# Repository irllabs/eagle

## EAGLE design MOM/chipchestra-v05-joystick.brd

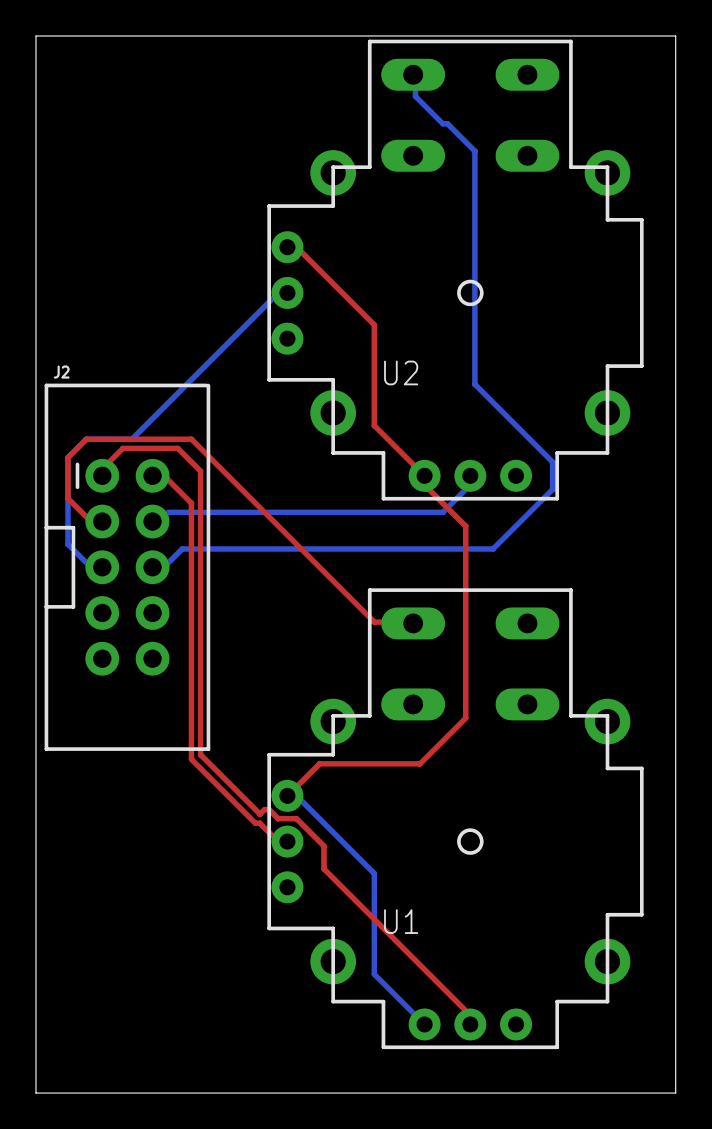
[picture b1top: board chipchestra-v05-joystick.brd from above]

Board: 2 copper layers, 35.5 x 58.7 mm, 3 parts (0 on the bottom side), 8 nets.

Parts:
J2: 2X5-SHROUDED_LOCK
U1, U2: JOYSTICKPTH; JOYSTICK

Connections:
+5V: U1.H1, U1.V1, U2.H1, U2.V1
GND: J2.10, U1.B2A, U1.H3, U1.V3, U2.B2A, U2.H3, U2.V3
JOYB1: J2.3, U1.B1A
JOYB2: J2.6, U2.B1A
JOYH1: J2.1, U1.H2
JOYH2: J2.4, U2.H2
JOYV1: J2.2, U1.V2
JOYV2: J2.5, U2.V2

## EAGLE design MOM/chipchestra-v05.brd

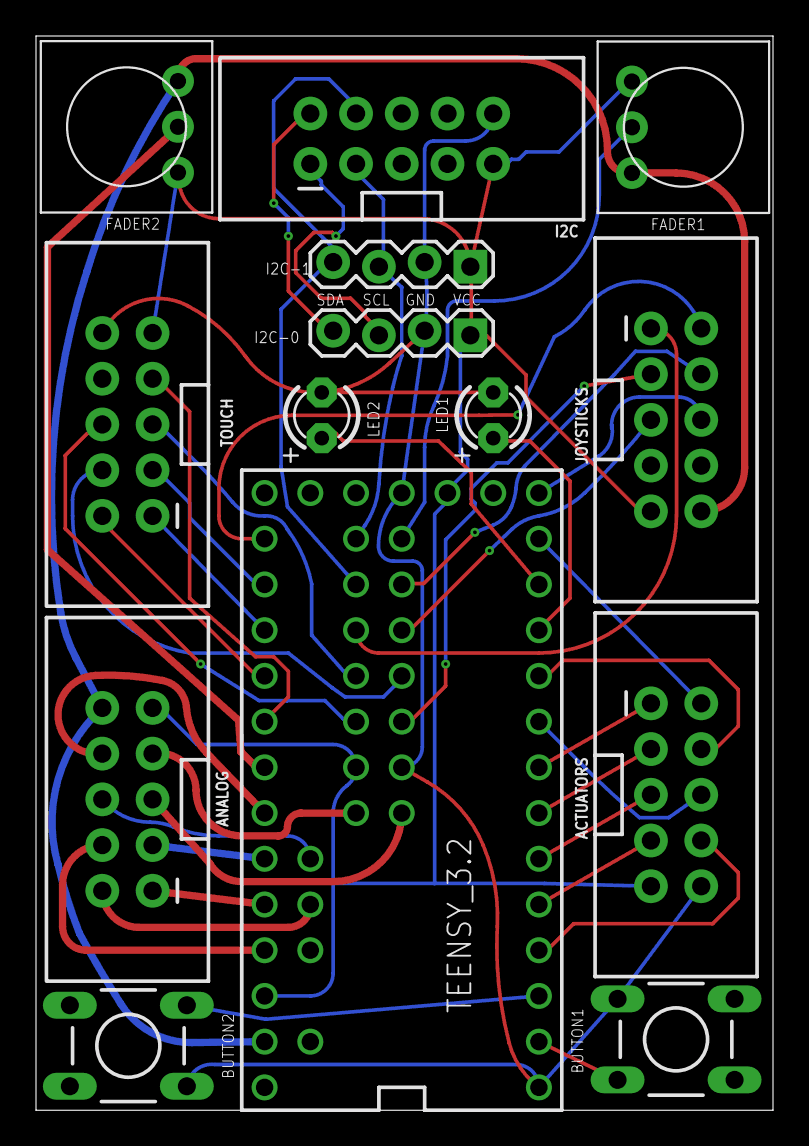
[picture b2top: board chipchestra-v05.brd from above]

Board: 2 copper layers, 40.9 x 59.7 mm, 14 parts (0 on the bottom side), 42 nets.

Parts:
ACTUATORS: 2X5-SHROUDED_LOCK
ANALOG: 2X5-SHROUDED_LOCK
BUTTON1, BUTTON2: DTS-6
FADER1, FADER2: TRIM-3386
I2C: 2X5-SHROUDED_LOCK
I2C-0, I2C-1: 1X04_LOCK
JOYSTICKS: 2X5-SHROUDED_LOCK
LED1, LED2: LED3MM
TEENSY_3.2: TEENSY_3.1-3.2_ALL_PINS&PADS; TEENSY_3.0-3.2_ALL_PINS_&_PADS
TOUCH: 2X5-SHROUDED_LOCK

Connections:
+3V3: ACTUATORS.9, ANALOG.9, FADER1.1, FADER2.1, I2C.9, I2C-0.1, I2C-1.1, JOYSTICKS.9, TEENSY_3.2.3.3V, TEENSY_3.2.3.3V1, TEENSY_3.2.3.3V2, TOUCH.9
AGND: ANALOG.10, FADER1.3, FADER2.3, JOYSTICKS.10, TEENSY_3.2.AGND
ANALOG1: ANALOG.1, TEENSY_3.2.22/A8
ANALOG2: ANALOG.2, TEENSY_3.2.A10
ANALOG3: ANALOG.3, TEENSY_3.2.21/A7
ANALOG4: ANALOG.4, TEENSY_3.2.23/A9
ANALOG5: ANALOG.5, TEENSY_3.2.A12
ANALOG6: ANALOG.6, TEENSY_3.2.A11
ANALOG7: ANALOG.7, TEENSY_3.2.A13
ANALOG8: ANALOG.8, TEENSY_3.2.20/A6
BUTTON1: BUTTON1.3, TEENSY_3.2.0
BUTTON2: BUTTON2.3, TEENSY_3.2.1
FADER1: FADER1.2, TEENSY_3.2.28
FADER2: FADER2.2, TEENSY_3.2.19/A5
GND: ACTUATORS.10, BUTTON1.1, BUTTON2.1, I2C.10, I2C-0.2, I2C-1.2, LED1.K, LED2.K, TEENSY_3.2.GND, TEENSY_3.2.GND1, TEENSY_3.2.GND2, TOUCH.10
I2C_SCL0: I2C.1, I2C-0.3
I2C_SCL1: I2C.3, I2C-1.3, TEENSY_3.2.29
I2C_SDA0: I2C.2, I2C-0.4
I2C_SDA1: I2C.4, I2C-1.4, TEENSY_3.2.30
JOYB1: JOYSTICKS.3, TEENSY_3.2.24
JOYB2: JOYSTICKS.6, TEENSY_3.2.12
JOYH1: JOYSTICKS.1, TEENSY_3.2.31
JOYH2: JOYSTICKS.4, TEENSY_3.2.27
JOYV1: JOYSTICKS.2, TEENSY_3.2.14/A0
JOYV2: JOYSTICKS.5, TEENSY_3.2.26
LED1: LED1.A, TEENSY_3.2.9
LED2: LED2.A, TEENSY_3.2.10
MOT_AIN_1: ACTUATORS.2, TEENSY_3.2.11
MOT_AIN_2: ACTUATORS.6, TEENSY_3.2.7
MOT_BIN_1: ACTUATORS.4, TEENSY_3.2.8
MOT_BIN_2: ACTUATORS.8, TEENSY_3.2.2
MOT_PWMA_1: ACTUATORS.1, TEENSY_3.2.6
MOT_PWMA_2: ACTUATORS.5, TEENSY_3.2.4
MOT_PWMB_1: ACTUATORS.3, TEENSY_3.2.5
MOT_PWMB_2: ACTUATORS.7, TEENSY_3.2.3
TOUCH1: TEENSY_3.2.16/A2, TOUCH.1
TOUCH2: TEENSY_3.2.17/A3, TOUCH.2
TOUCH3: TEENSY_3.2.15/A1, TOUCH.3
TOUCH4: TEENSY_3.2.25, TOUCH.4
TOUCH5: TEENSY_3.2.32, TOUCH.5
TOUCH6: TEENSY_3.2.33, TOUCH.6
TOUCH7: TEENSY_3.2.18/A4, TOUCH.7

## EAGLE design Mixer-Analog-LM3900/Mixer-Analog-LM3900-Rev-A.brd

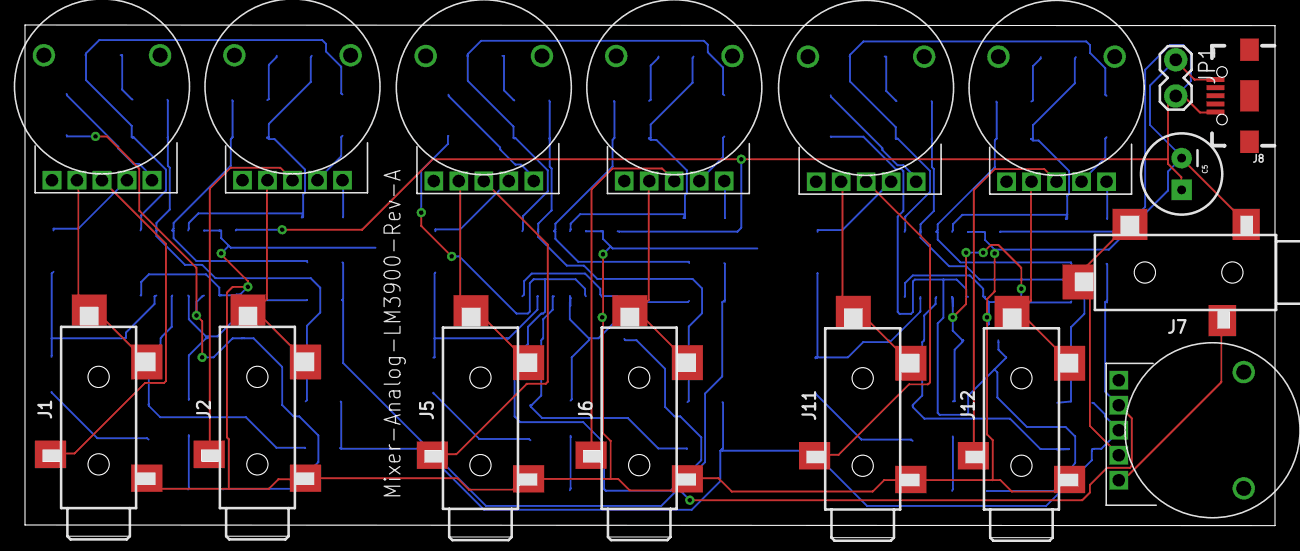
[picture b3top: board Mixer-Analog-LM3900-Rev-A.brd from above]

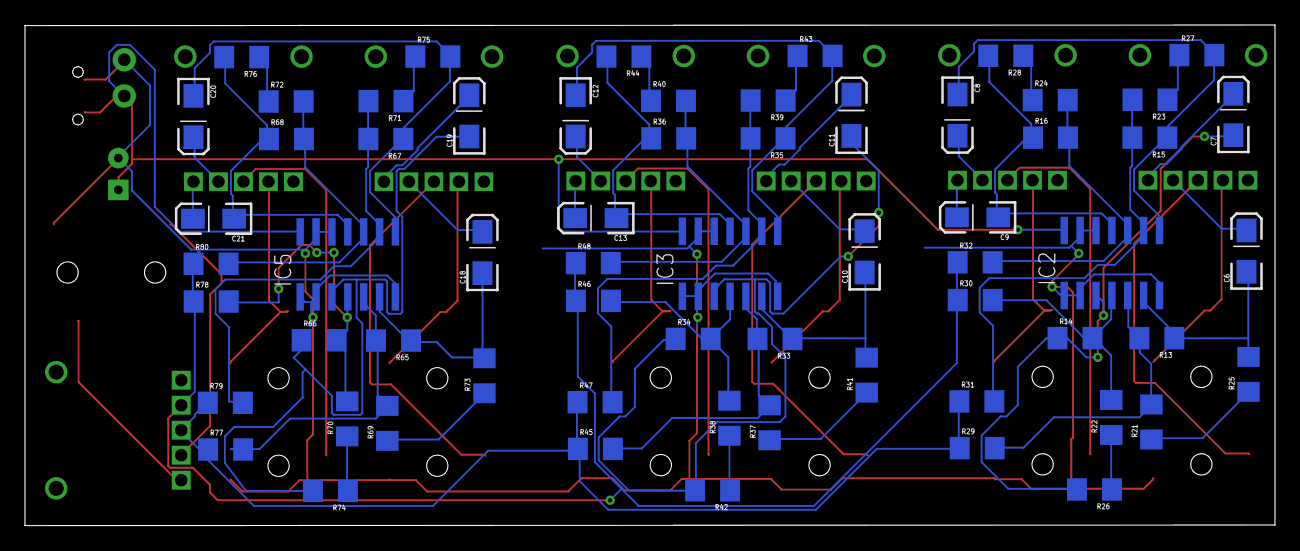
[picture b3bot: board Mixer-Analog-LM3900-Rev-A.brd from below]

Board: 2 copper layers, 100.0 x 40.0 mm, 80 parts (63 on the bottom side), 66 nets.

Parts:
C5: CPOL-RADIAL-100UF-25V
C6, C7, C8, C9, C10, C11, C12, C13, C18, C19, C20, C21: 0.47u; EIA3216-KIT
IC2, IC3, IC5: LM3900D; SO14
J1, J2, J5, J6, J7, J11, J12: SJ-3524-SMT
J8: USB-B-MICRO-SMD
JP1: 1X02_LOCK
R13, R14, R15, R16, R33, R34, R35, R36, R65, R66, R67, R68: 1M; 1206
R21, R22, R23, R24, R37, R38, R39, R40, R69, R70, R71, R72: 330; 1206
R25, R26, R27, R28, R29, R30, R31, R32, R41, R42, R43, R44, R45, R46, R47, R48, R73, R74, R75, R76, R77, R78, R79, R80: 470; 1206
U$3, U$4, U$5, U$6, U$7, U$10, U$11: POT-DUAL-ALPS-RK10J12E0A0A

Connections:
5V: C5.1, IC2.14, IC3.14, IC5.14, J8.VBUS, JP1.2
GND: C5.2, IC2.1, IC2.2, IC2.7, IC2.12, IC2.13, IC3.1, IC3.2, IC3.7, IC3.12, IC3.13, IC5.1, IC5.2, IC5.7, IC5.12, IC5.13, J1.1, J2.1, J5.1, J6.1, J7.1, J8.GND, J11.1, J12.1, JP1.1
unnamed: IC2.5, R13.2, R21.2, R29.2
unnamed: C6.C, IC2.6, R13.1, R25.2
unnamed: R21.1, R25.1
unnamed: IC2.4, R14.2, R22.2, R30.2
unnamed: C7.C, IC2.3, R14.1, R26.2
unnamed: R22.1, R26.1
unnamed: IC2.9, R15.2, R23.2, R31.2
unnamed: C8.C, IC2.8, R15.1, R27.2
unnamed: R23.1, R27.1
unnamed: IC2.10, R16.2, R24.2, R32.2
unnamed: C9.C, IC2.11, R16.1, R28.2
unnamed: R24.1, R28.1
unnamed: C9.A, U$3.P$5
unnamed: C8.A, U$3.P$4
unnamed: C7.A, U$4.P$5
unnamed: C6.A, U$4.P$4
unnamed: J1.2, J1.4, U$4.P$2
unnamed: J2.2, J2.4, U$3.P$2
unnamed: J2.3, U$3.P$3
unnamed: J1.3, U$4.P$3
unnamed: IC3.5, R33.2, R37.2, R45.2
unnamed: C10.C, IC3.6, R33.1, R41.2
unnamed: R37.1, R41.1
unnamed: IC3.4, R34.2, R38.2, R46.2
unnamed: C11.C, IC3.3, R34.1, R42.2
unnamed: R38.1, R42.1
unnamed: IC3.9, R35.2, R39.2, R47.2
unnamed: C12.C, IC3.8, R35.1, R43.2
unnamed: R39.1, R43.1
unnamed: IC3.10, R36.2, R40.2, R48.2
unnamed: C13.C, IC3.11, R36.1, R44.2
unnamed: R40.1, R44.1
unnamed: C13.A, U$5.P$5
unnamed: C12.A, U$5.P$4
unnamed: C11.A, U$6.P$5
unnamed: C10.A, U$6.P$4
unnamed: J5.2, J5.4, U$6.P$2
unnamed: J6.2, J6.4, U$5.P$2
unnamed: J7.2, J7.4, U$7.P$4
unnamed: J7.3, U$7.P$5
unnamed: J6.3, U$5.P$3
unnamed: J5.3, U$6.P$3
unnamed: IC5.5, R65.2, R69.2, R77.2
unnamed: C18.C, IC5.6, R65.1, R73.2
unnamed: R69.1, R73.1
unnamed: IC5.4, R66.2, R70.2, R78.2
unnamed: C19.C, IC5.3, R66.1, R74.2
unnamed: R70.1, R74.1
unnamed: IC5.9, R67.2, R71.2, R79.2
unnamed: C20.C, IC5.8, R67.1, R75.2
unnamed: R71.1, R75.1
unnamed: IC5.10, R68.2, R72.2, R80.2
unnamed: C21.C, IC5.11, R68.1, R76.2
unnamed: R72.1, R76.1
unnamed: C21.A, U$10.P$5
unnamed: C20.A, U$10.P$4
unnamed: C19.A, U$11.P$5
unnamed: C18.A, U$11.P$4
unnamed: J11.2, J11.4, U$11.P$2
unnamed: J12.2, J12.4, U$10.P$2
unnamed: J12.3, U$10.P$3
unnamed: J11.3, U$11.P$3
unnamed: R29.1, R31.1, R45.1, R47.1, R77.1, R79.1, U$7.P$3
unnamed: R30.1, R32.1, R46.1, R48.1, R78.1, R80.1, U$7.P$2

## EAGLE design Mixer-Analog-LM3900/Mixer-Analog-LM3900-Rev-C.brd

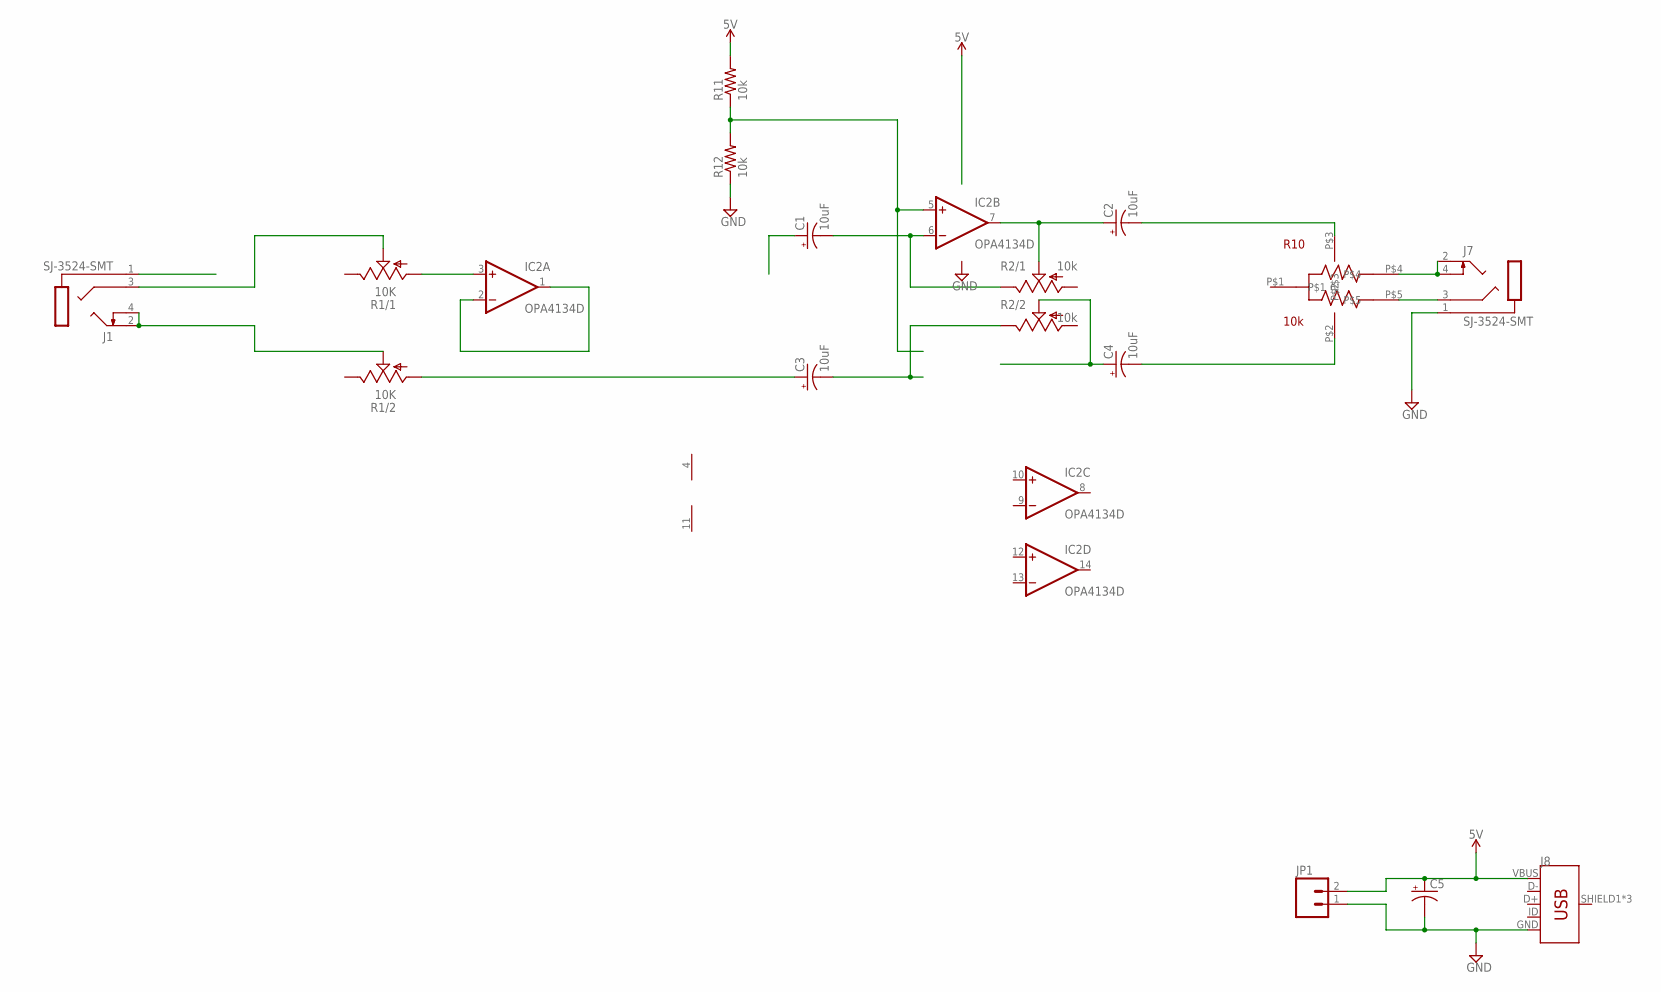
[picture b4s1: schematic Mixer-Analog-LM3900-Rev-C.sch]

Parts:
C1, C2, C3, C4: 10uF; EIA3216-KIT
C5: CAP_POLPTH1; CPOL-RADIAL-100UF-25V
IC2: OPA4134D; SO14
J1, J7: SJ-3524-SMT
J8: USB_MICRO-B_FEMALE-SMT; USB-B-MICRO-SMD
JP1: M02LOCK; 1X02_LOCK
R1: 10K; PTV112
R2: 10k; PTV112
R10: 10k; POT-DUAL-ALPS-RK10J12E0A0A
R11, R12: 10k; 1206

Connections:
5V: C5.1 (+), J8.VBUS, JP1.2, R11.2
DLE: C2.A (+), IC2.7 (OUT), R2.1.2 (S)
GND: C5.2 (-), J7.1 (S), J8.GND, JP1.1, R12.1
unnamed: C3.C (-), R2.2.3 (E)
unnamed: IC2.5 (+IN), R11.1, R12.2
unnamed: IC2.3 (+IN), R1.1.1 (A)
unnamed: IC2.1 (OUT), IC2.2 (-IN)
unnamed: C4.C (-), R10.P$2
unnamed: C1.C (-), IC2.6 (-IN), R2.1.3 (E)
unnamed: C4.A (+), R2.2.2 (S)
unnamed: C3.A (+), R1.2.1 (A)
unnamed: J1.2 (T), J1.4 (TS), R1.2.2 (S)
unnamed: J1.3 (R), R1.1.2 (S)
unnamed: J7.2 (T), J7.4 (TS), R10.P$4
unnamed: J7.3 (R), R10.P$5
unnamed: C2.C (-), R10.P$3
V+: IC2.4 (V+)
V-: IC2.11 (V-)

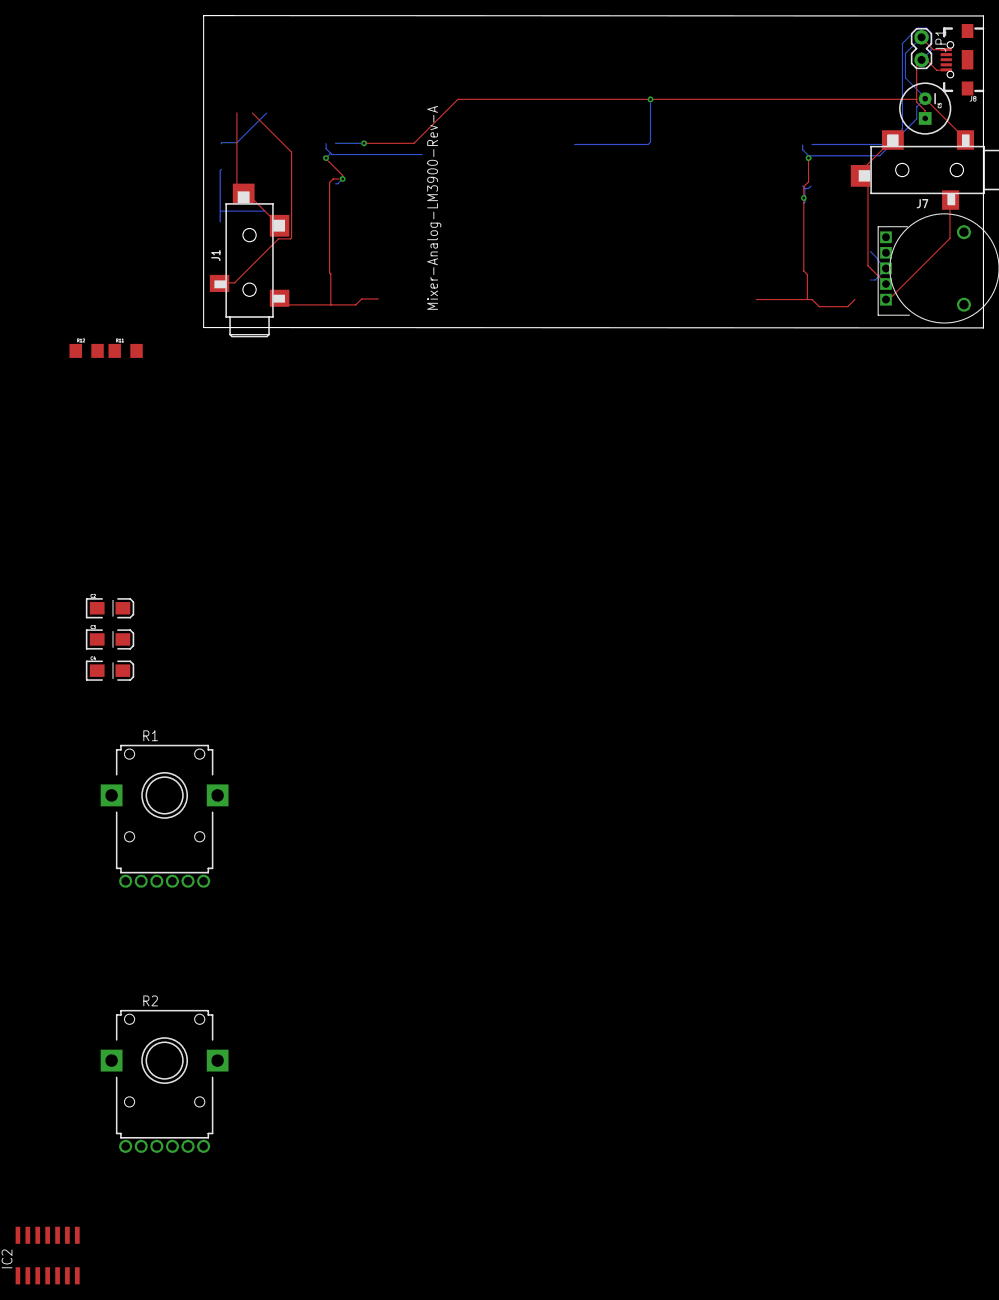
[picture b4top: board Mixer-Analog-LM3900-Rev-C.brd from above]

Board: 2 copper layers, 100.0 x 40.0 mm, 15 parts (1 on the bottom side), 16 nets.

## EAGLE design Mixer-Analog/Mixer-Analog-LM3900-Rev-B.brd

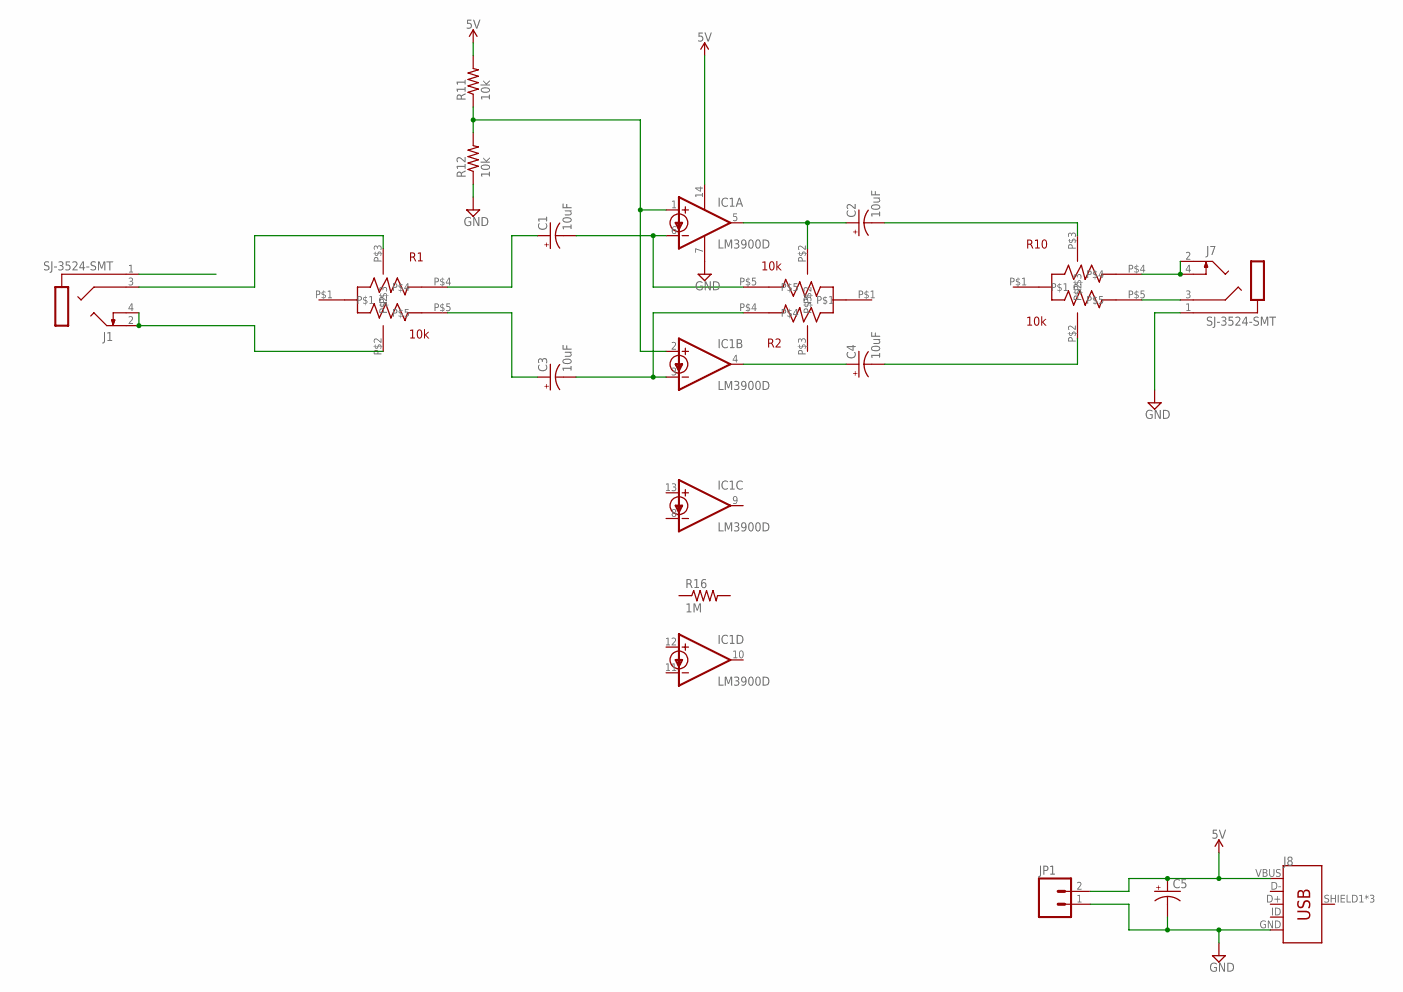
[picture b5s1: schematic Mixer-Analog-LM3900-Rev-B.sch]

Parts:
C1, C2, C3, C4: 10uF; EIA3216-KIT
C5: CAP_POLPTH1; CPOL-RADIAL-100UF-25V
IC1: LM3900D; SO14
J1, J7: SJ-3524-SMT
J8: USB_MICRO-B_FEMALE-SMT; USB-B-MICRO-SMD
JP1: M02LOCK; 1X02_LOCK
R1, R2, R10: 10k; POT-DUAL-ALPS-RK10J12E0A0A
R11, R12: 10k; 1206
R16: 1M; 1206

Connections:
5V: C5.1 (+), IC1.14 (V+), J8.VBUS, JP1.2, R11.2
GND: C5.2 (-), IC1.7 (GND), J7.1 (S), J8.GND, JP1.1, R12.1
unnamed: C3.C (-), IC1.3 (-IN), R2.P$4
unnamed: IC1.1 (+IN), IC1.2 (+IN), R11.1, R12.2
unnamed: C4.C (-), R10.P$2
unnamed: C2.A (+), IC1.5 (OUT), R2.P$2
unnamed: C1.C (-), IC1.6 (-IN), R2.P$5
unnamed: C4.A (+), IC1.4 (OUT)
unnamed: C3.A (+), R1.P$5
unnamed: C1.A (+), R1.P$4
unnamed: J1.2 (T), J1.4 (TS), R1.P$2
unnamed: J1.3 (R), R1.P$3
unnamed: J7.2 (T), J7.4 (TS), R10.P$4
unnamed: J7.3 (R), R10.P$5
unnamed: C2.C (-), R10.P$3

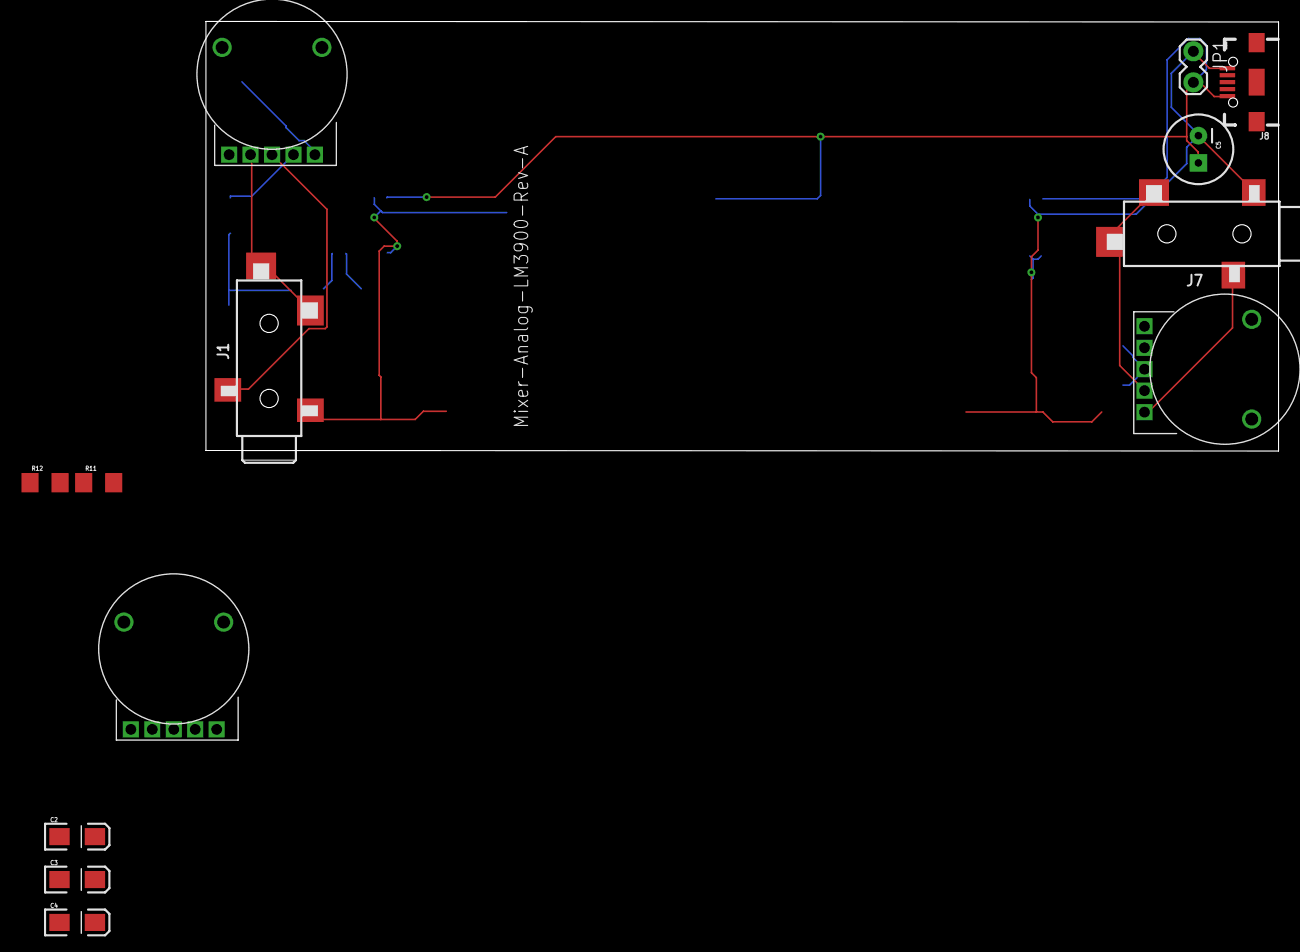
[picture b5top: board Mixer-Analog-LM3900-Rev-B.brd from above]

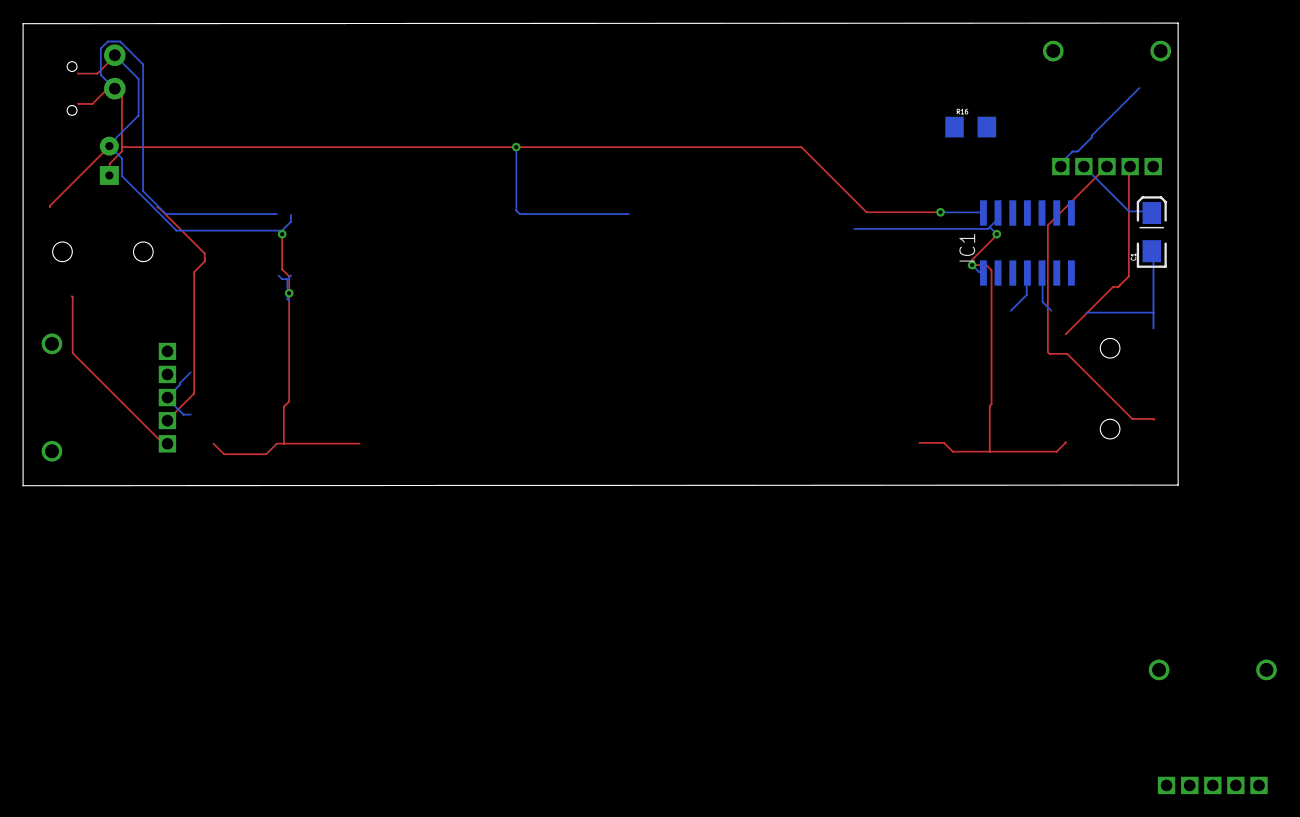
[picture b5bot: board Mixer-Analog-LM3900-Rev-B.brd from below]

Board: 2 copper layers, 100.0 x 40.0 mm, 16 parts (3 on the bottom side), 15 nets.

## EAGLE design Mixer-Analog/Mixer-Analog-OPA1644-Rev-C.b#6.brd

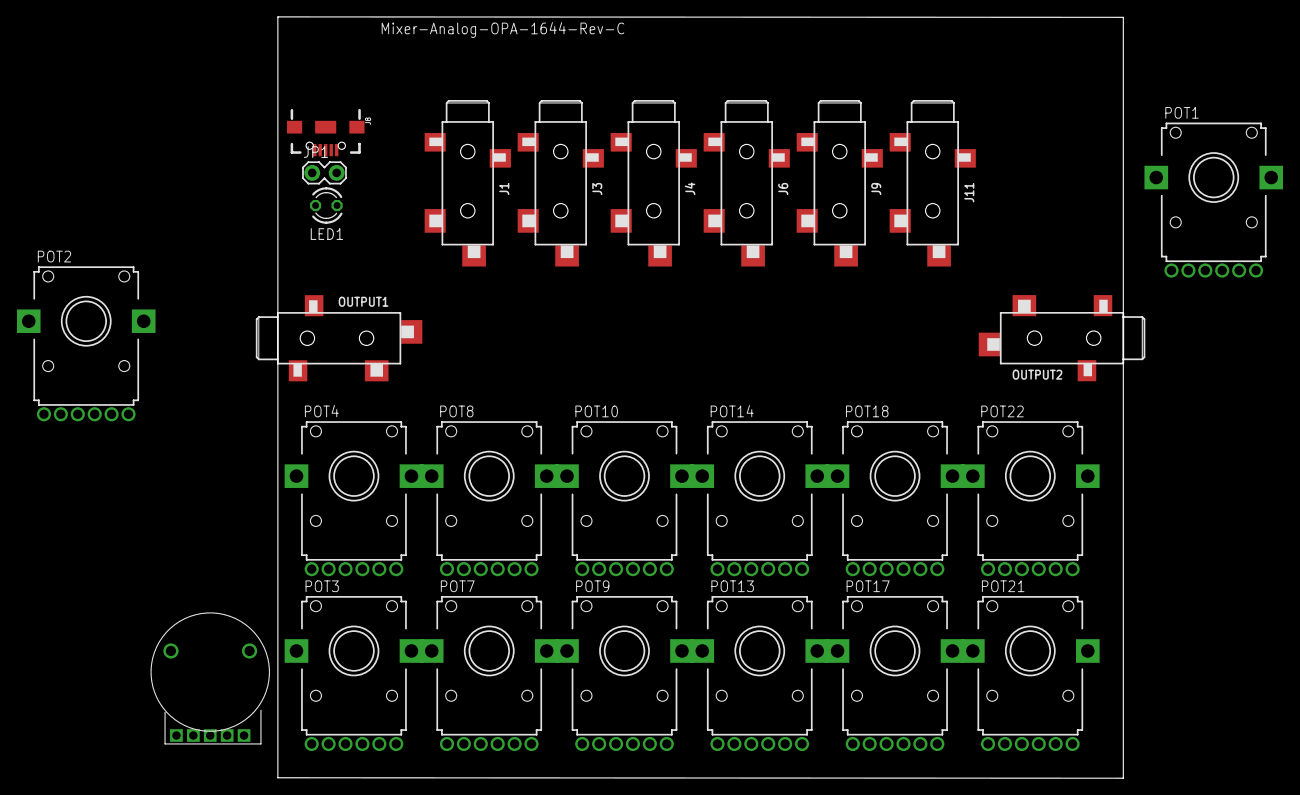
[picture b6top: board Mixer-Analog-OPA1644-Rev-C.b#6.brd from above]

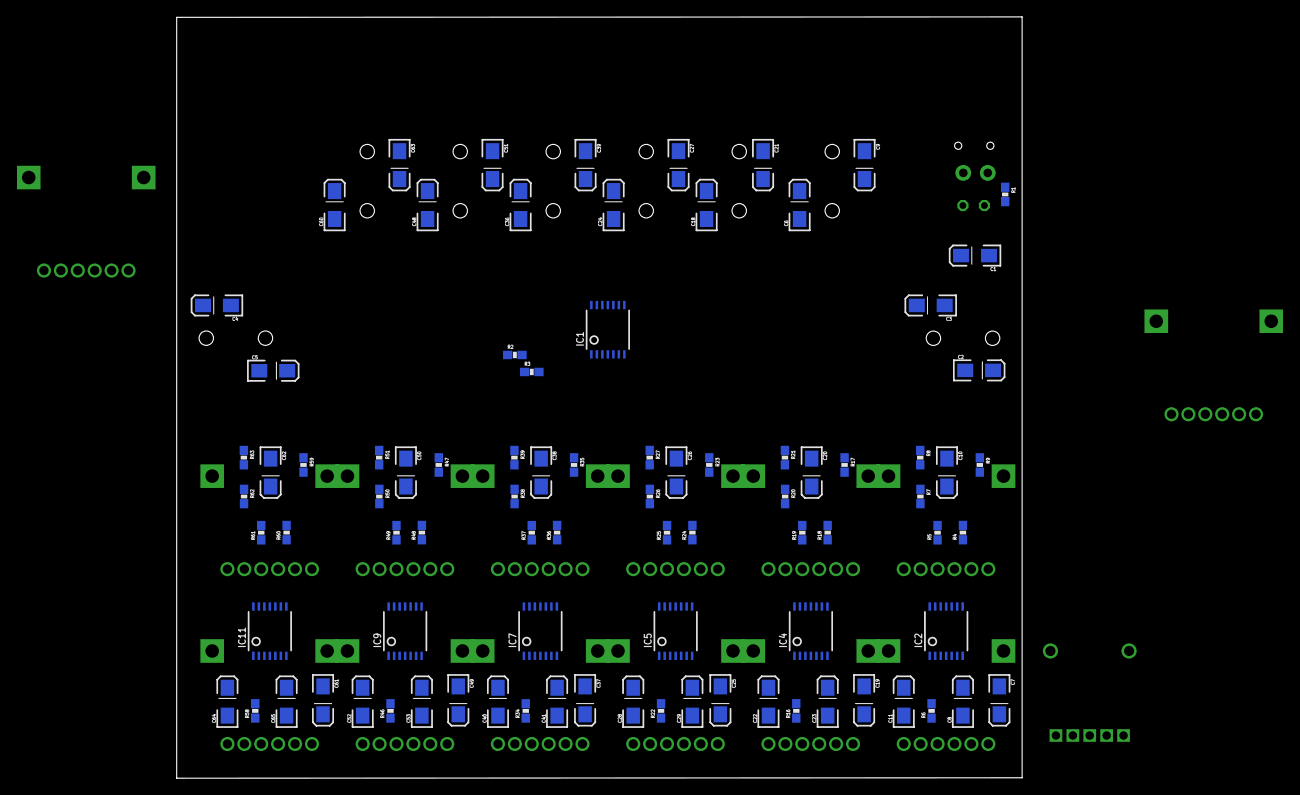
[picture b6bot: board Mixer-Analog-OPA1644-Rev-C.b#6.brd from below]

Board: 2 copper layers, 100.0 x 90.0 mm, 113 parts (87 on the bottom side), 98 nets, no tracks yet.

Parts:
C1, C2, C3, C4, C5, C6, C7, C8, C9, C10, C11, C18, C19, C20, C21, C22, C23, C24, C25, C26, C27, C28, C29, C36, C37, C38, C39, C40, C41, C48, C49, C50, C51, C52, C53, C60, C61, C62, C63, C64, C65: 10uF; EIA3216-KIT
IC1, IC2, IC4, IC5, IC7, IC9, IC11: OPA1644; TSSOP14
J1, J3, J4, J6, J9, J11: SJ-3524-SMT
J8: USB-B-MICRO-SMD
JP1: 1X02_LOCK
LED1: LED3MM
OUTPUT1, OUTPUT2: SJ-3524-SMT
POT1, POT2: 10k; PTV112
POT3, POT7, POT9, POT13, POT17, POT21: 10K; PTV112
POT4, POT8, POT10, POT14, POT18, POT22: 100K; PTV112
R1: 220; 0603-RES
R2, R3, R4, R5, R7, R8, R18, R19, R20, R21, R24, R25, R26, R27, R36, R37, R38, R39, R48, R49, R50, R51, R60, R61, R62, R63: 1M; 0603-RES
R6, R9, R16, R17, R22, R23, R34, R35, R46, R47, R58, R59: 10k; 0603-RES
U$1: POT-DUAL-ALPS-RK10J12E0A0A

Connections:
5V: C1.A, IC1.4, IC2.4, IC4.4, IC5.4, IC7.4, IC9.4, IC11.4, J8.VBUS, JP1.2, LED1.A, R3.2, R4.2, R7.2, R18.2, R20.2, R24.2, R26.2, R36.2, R38.2, R48.2, R50.2, R60.2, R62.2
COPY\: IC2.1, IC2.2, POT3.1.3
COPY\2: IC4.1, IC4.2, POT7.1.3
COPY\3: IC5.1, IC5.2, POT9.1.3
COPY\5: IC7.1, IC7.2, POT13.1.3
COPY\7: IC9.1, IC9.2, POT17.1.3
COPY\9: IC11.1, IC11.2, POT21.1.3
DLE: C8.A, IC2.7, POT4.1.2
DLE2: C23.A, IC4.7, POT8.1.2
DLE3: C29.A, IC5.7, POT10.1.2
DLE5: C41.A, IC7.7, POT14.1.2
DLE7: C53.A, IC9.7, POT18.1.2
DLE9: C65.A, IC11.7, POT22.1.2
GND: C1.C, IC1.11, IC2.11, IC4.11, IC5.11, IC7.11, IC9.11, IC11.11, J8.GND, JP1.1, OUTPUT1.1, OUTPUT2.1, POT3.1.1, POT3.2.1, POT7.1.1, POT7.2.1, POT9.1.1, POT9.2.1, POT13.1.1, POT13.2.1, POT17.1.1, POT17.2.1, POT21.1.1, POT21.2.1, R1.1, R2.1, R5.1, R8.1, R19.1, R21.1, R25.1, R27.1, R37.1, R39.1, R49.1, R51.1, R61.1, R63.1
unnamed: IC2.13, POT4.2.3, R9.2
unnamed: C7.A, POT3.1.2
unnamed: IC2.6, POT4.1.3, R6.2
unnamed: C6.C, IC2.3, R4.1, R5.2
unnamed: C2.A, IC1.1, POT1.1.2
unnamed: C7.C, R6.1
unnamed: IC2.8, IC2.9, POT3.2.3
unnamed: C6.A, J1.3
unnamed: C9.C, IC2.10, R7.1, R8.2
unnamed: C9.A, J1.2, J1.4
unnamed: C10.A, POT3.2.2
unnamed: C10.C, R9.1
unnamed: LED1.K, R1.2
unnamed: C3.A, IC1.7, POT1.2.2
unnamed: C4.C, OUTPUT2.2, OUTPUT2.4
unnamed: C5.C, OUTPUT2.3
unnamed: C4.A, IC1.8, POT2.1.2
unnamed: C5.A, IC1.14, POT2.2.2
unnamed: C11.A, IC2.14, POT4.2.2
unnamed: C22.A, IC4.14, POT8.2.2
unnamed: IC4.13, POT8.2.3, R17.2
unnamed: IC4.8, IC4.9, POT7.2.3
unnamed: C21.A, J3.2, J3.4
unnamed: C18.C, IC4.3, R18.1, R19.2
unnamed: C18.A, J3.3
unnamed: C21.C, IC4.10, R20.1, R21.2
unnamed: C19.A, POT7.1.2
unnamed: C19.C, R16.1
unnamed: IC4.6, POT8.1.3, R16.2
unnamed: C20.A, POT7.2.2
unnamed: C20.C, R17.1
unnamed: C28.A, IC5.14, POT10.2.2
unnamed: IC5.13, POT10.2.3, R23.2
unnamed: IC5.8, IC5.9, POT9.2.3
unnamed: C27.A, J4.2, J4.4
unnamed: C24.C, IC5.3, R24.1, R25.2
unnamed: C24.A, J4.3
unnamed: C27.C, IC5.10, R26.1, R27.2
unnamed: C25.A, POT9.1.2
unnamed: C25.C, R22.1
unnamed: IC5.6, POT10.1.3, R22.2
unnamed: C26.A, POT9.2.2
unnamed: C26.C, R23.1
unnamed: C2.C, OUTPUT1.2, OUTPUT1.4
unnamed: C3.C, OUTPUT1.3
unnamed: C40.A, IC7.14, POT14.2.2
unnamed: IC7.13, POT14.2.3, R35.2
unnamed: IC7.8, IC7.9, POT13.2.3
unnamed: C39.A, J6.2, J6.4
unnamed: C36.C, IC7.3, R36.1, R37.2
unnamed: C36.A, J6.3
unnamed: C39.C, IC7.10, R38.1, R39.2
unnamed: C37.A, POT13.1.2
unnamed: C37.C, R34.1
unnamed: IC7.6, POT14.1.3, R34.2
unnamed: C38.A, POT13.2.2
unnamed: C38.C, R35.1
unnamed: C52.A, IC9.14, POT18.2.2
unnamed: IC9.13, POT18.2.3, R47.2
unnamed: IC9.8, IC9.9, POT17.2.3
unnamed: C51.A, J9.2, J9.4
unnamed: C48.C, IC9.3, R48.1, R49.2
unnamed: C48.A, J9.3
unnamed: C51.C, IC9.10, R50.1, R51.2
unnamed: C49.A, POT17.1.2
unnamed: C49.C, R46.1
unnamed: IC9.6, POT18.1.3, R46.2
unnamed: C50.A, POT17.2.2
unnamed: C50.C, R47.1
unnamed: C64.A, IC11.14, POT22.2.2
unnamed: IC11.13, POT22.2.3, R59.2
unnamed: IC11.8, IC11.9, POT21.2.3
unnamed: C63.A, J11.2, J11.4
unnamed: C60.C, IC11.3, R60.1, R61.2
unnamed: C60.A, J11.3
unnamed: C63.C, IC11.10, R62.1, R63.2
unnamed: C61.A, POT21.1.2
unnamed: C61.C, R58.1
unnamed: IC11.6, POT22.1.3, R58.2
unnamed: C62.A, POT21.2.2
unnamed: C62.C, R59.1
OUT-L: C8.C, C23.C, C29.C, C41.C, C53.C, C65.C, IC1.2, IC1.9, POT1.1.3, POT2.1.3
OUT-R: C11.C, C22.C, C28.C, C40.C, C52.C, C64.C, IC1.6, IC1.13, POT1.2.3, POT2.2.3
VGND: IC1.3, IC1.5, IC1.10, IC1.12, IC2.5, IC2.12, IC4.5, IC4.12, IC5.5, IC5.12, IC7.5, IC7.12, IC9.5, IC9.12, IC11.5, IC11.12, R2.2, R3.1

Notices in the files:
parts and their libraries:
SparkFun-Connectors: Licensing: Creative Commons ShareAlike 4.0 International - https://creativecommons.org/licenses/by-sa/4.0
con-cuistack: Copyright (C) 2008, Bob Starr
